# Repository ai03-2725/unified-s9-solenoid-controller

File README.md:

## **Unified-S9 9V Solenoid Driver**

**Note:** Prototype not confirmed functional. Please modify to function before producing.

Based on [Xwhatit's work](https://geekhack.org/index.php?topic=58192), modified to work natively through QMK's haptic feedback/solenoid implementation.  
Open-source and extremely compacted to be easily implementable by custom keyboard designers.  

All credits for the original circuitry goes to Xwhatsit (source viewable [here](https://github.com/BASLQC/xwhatits-capsense-controller)).  
Many credits to Gondolindrim and Wilba for assistance along the way.

For the rest of the unified daughterboard series, see [here](https://github.com/ai03-2725/Unified-Daughterboard).

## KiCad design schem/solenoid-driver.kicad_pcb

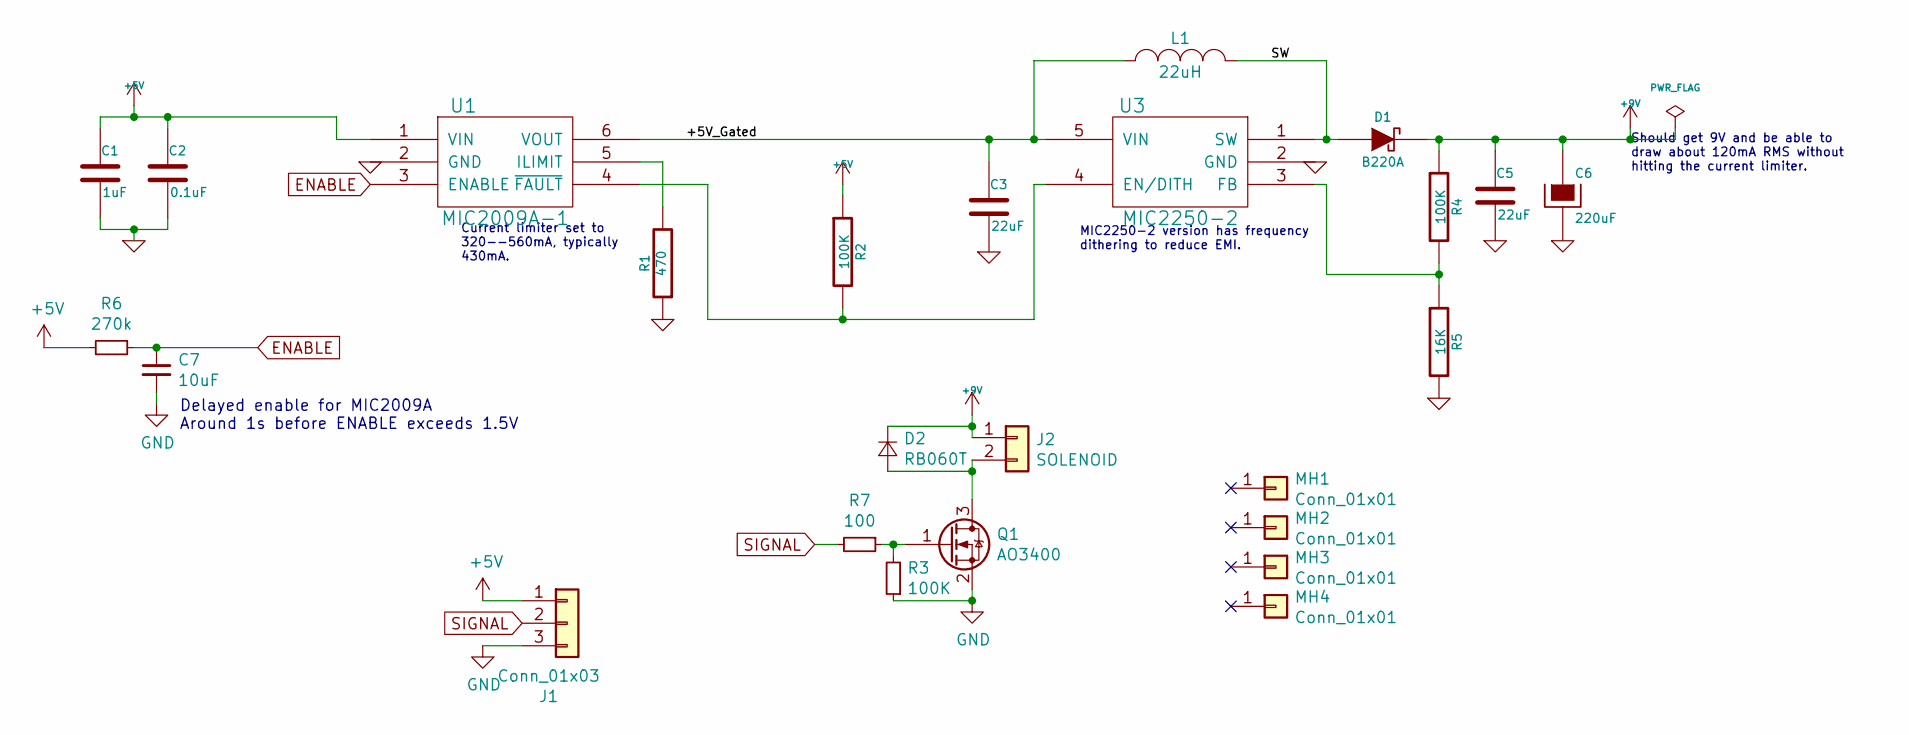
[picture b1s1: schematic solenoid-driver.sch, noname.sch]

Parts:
C1: 1uF; C_0805_2012Metric
C2: 0.1uF; C_0805_2012Metric
C3, C5: 22uF; C_1206_3216Metric
C6: 220uF; CP_Elec_6.3x7.7
C7: 10uF; C_0805_2012Metric
D1: B220A; D_SMA
D2: RB060T; D_SOD-123
J1: Conn_01x03; JST-SR-3
J2: SOLENOID; PinHeader_1x02_P2.54mm_Vertical
L1: 22uH; L_12x12mm_H6mm
MH1, MH2, MH3, MH4: Conn_01x01; Generic-Mounthole
Q1: AO3400; SOT-23
R1: 470; R_0805_2012Metric
R2, R3, R4: 100K; R_0805_2012Metric
R5: 16K; R_0805_2012Metric
R6: 270k; R_0805_2012Metric
R7: 100; R_0805_2012Metric
U1: MIC2009A-1; SOT-23-6
U3: MIC2250-2; SOT-23-5

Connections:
+5V: C1.1, C2.1, J1.1, R2.1, R6.2, U1.1 (VIN)
+9V: C5.1, C6.1, D1.2 (K), D2.1 (K), J2.1, R4.1
/+5V_Gated: C3.1, L1.1, U1.6 (VOUT), U3.5 (VIN)
/SW: D1.1 (A), L1.2, U3.1 (SW)
ENABLE: C7.1, R6.1, U1.3 (ENABLE)
GND: C1.2, C2.2, C3.2, C5.2, C6.2, C7.2, J1.3, Q1.2 (S), R1.1, R3.1, R5.2, U1.2 (GND), U3.2 (GND)
unnamed: D2.2 (A), J2.2, Q1.3 (D)
unnamed: Q1.1 (G), R3.2, R7.1
unnamed: R1.2, U1.5 (ILIMIT)
unnamed: R2.2, U1.4 (~FAULT), U3.4 (EN/DITH)
unnamed: R4.2, R5.1, U3.3 (FB)
SIGNAL: J1.2, R7.2

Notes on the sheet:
Should get 9V and be able to draw about 120mA RMS without hitting the current limiter.
Current limiter set to 320--560mA, typically 430mA.
MIC2250-2 version has frequency dithering to reduce EMI.
Delayed enable for MIC2009A Around 1s before ENABLE exceeds 1.5V

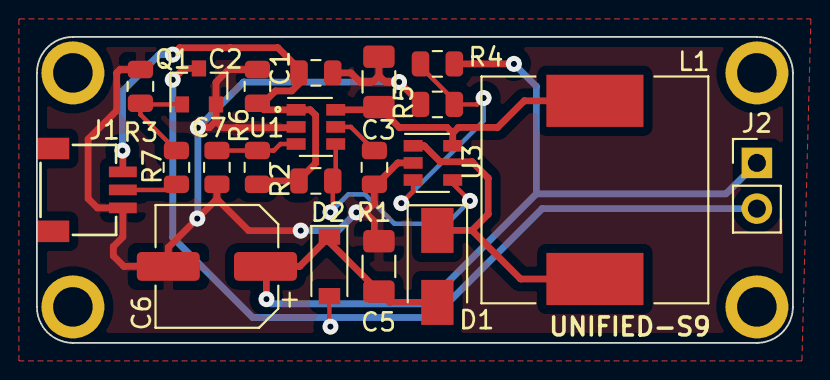
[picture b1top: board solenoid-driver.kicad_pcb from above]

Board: 2 copper layers, 42.0 x 17.0 mm, 25 parts (0 on the bottom side), 12 nets.

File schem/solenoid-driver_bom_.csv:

Component,Description,Part,References,Value,Footprint,Quantity Per PCB,Datasheet
1,,C,C2,0.1uF,C_0805_2012Metric,1,~
2,"Unpolarized capacitor, small symbol",C_Small,C7,10uF,C_0805_2012Metric,1,~
3,,C,C1,1uF,C_0805_2012Metric,1,~
4,,CP,C6,220uF,CP_Elec_6.3x7.7,1,~
5,,C,C3 C5,22uF,C_1206_3216Metric,2,~
6,,DIODESCH,D1,B220A,D_SMA,1,~
7,"Diode, small symbol",D_Small,D2,RB060T,D_SOD-123,1,~
8,"Generic connector, single row, 01x03, script generated (kicad-library-utils/schlib/autogen/connector/)",Conn_01x03,J1,Conn_01x03,JST-SR-3,1,~
9,"Generic connector, single row, 01x02, script generated (kicad-library-utils/schlib/autogen/connector/)",Conn_01x02,J2,SOLENOID,PinHeader_1x02_P2.54mm_Vertical,1,~
10,,INDUCTOR_SMALL,L1,22uH,L_12x12mm_H6mm,1,~
11,"N-MOSFET transistor, gate/source/drain",Q_NMOS_GSD,Q1,AO3400,SOT-23,1,~
12,"Resistor, small symbol",R_Small,R7,100,R_0805_2012Metric,1,~
13,,R,R2 R4,100K,R_0805_2012Metric,2,~
14,"Resistor, small symbol",R_Small,R3,100K,R_0805_2012Metric,1,~
15,,R,R5,16K,R_0805_2012Metric,1,~
16,"Resistor, small symbol",R_Small,R6,270k,R_0805_2012Metric,1,~
17,,R,R1,470,R_0805_2012Metric,1,~
18,,MIC2009A,U1,MIC2009A-1,SOT-23-6,1,~
19,,MIC2250,U3,MIC2250-2,SOT-23-5,1,





Component Groups:,19
Component Count:,21
Fitted Components:,21
Number of PCBs:,1
Total components:,21
Schematic Version:,
Schematic Date:,11 aug 2014
BoM Date:,3/30/2020 8:58:00 PM
Schematic Source:,C:\Users\Ryota Goto\Documents\GitHub\9V-solenoid-controller\schem\solenoid-driver.sch
KiCad Version:,Eeschema (5.1.4)-1

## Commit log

2020-03-24 Remove all but the solenoid controller files
2020-03-24 Update to KiCad 5.1.4 openable format
2020-03-24 Tune up schema
2020-03-24 Add lib submodule
2020-03-24 Update submods
2020-03-24 Route the PCB
2020-03-24 Finalize PCB
2020-03-24 Add barebones documentation
2020-03-24 Add gerbers
2020-03-31 Fix pinout and regenerate gerber
2020-04-16 Remove an unnecessary via

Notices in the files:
schem/solenoid-driver.kicad_pcb:
Original circuit by xwhatsit, licensed GPLv3
